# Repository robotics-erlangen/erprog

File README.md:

# ERPROG
This is a JTAG-Programmer developed by the Robot Soccer Team ER-Force from Erlangen, Germany.
The device is using a FTDI chip for communication and a digital isolator for the target.
All necessary files to build and control this device can be found within this repository.

The benefits of this hardware are the easy USB connection with EMC protection and over-current protection. Furthermore the standard JTAG output with a complete isolation up to 4kV. The target isolation is done by two ISO7231M from Texas Instruments. This device also does a voltage translation, which adapts to the target voltage-level. Working is guaranteed from 3.2 to 5.4V.
With this circuit the computer is never effected, if the programming target fails in any way.

Project origin: https://www.robotics-erlangen.de/publications/jtag-programmer

## Hardware

The PCB is designed with EAGLE. The schematic can be found in `erprog_1504-1.sch` and the board in `erprog_1504-1.brd`. The dimension of the PCB is 850mil x 2300mil.

The main ICs are

1.  FT4232HL does the USB to JTAG conversation
2.  ISO7231 is the digital isolator

## Software

The software readme is in https://github.com/robotics-erlangen/erprog/tree/master/software

## Computer connection

**via USB**

The device is connected via a Mini-USB plug to the computer.

## Target connection

**via JTAG**

This hardware uses a JTAG standard connector with a 10 pin connector with the `CoreSight 10` pinout.
Follwoing the pinout is described based on a standard 10 pin 100mil plug with 2 rows.

1.  VTREF
2.  TMS
3.  GND
4.  TCK
5.  GND
6.  TDO
7.  NC
8.  TDI
9.  GND
10. nSRST

## ToDo

For the next release it is planned to allow the controlling of the isolator's enable-pin. Thus, the programmer can be put into high-impedance mode so it does not interfere with the target in normal operation.

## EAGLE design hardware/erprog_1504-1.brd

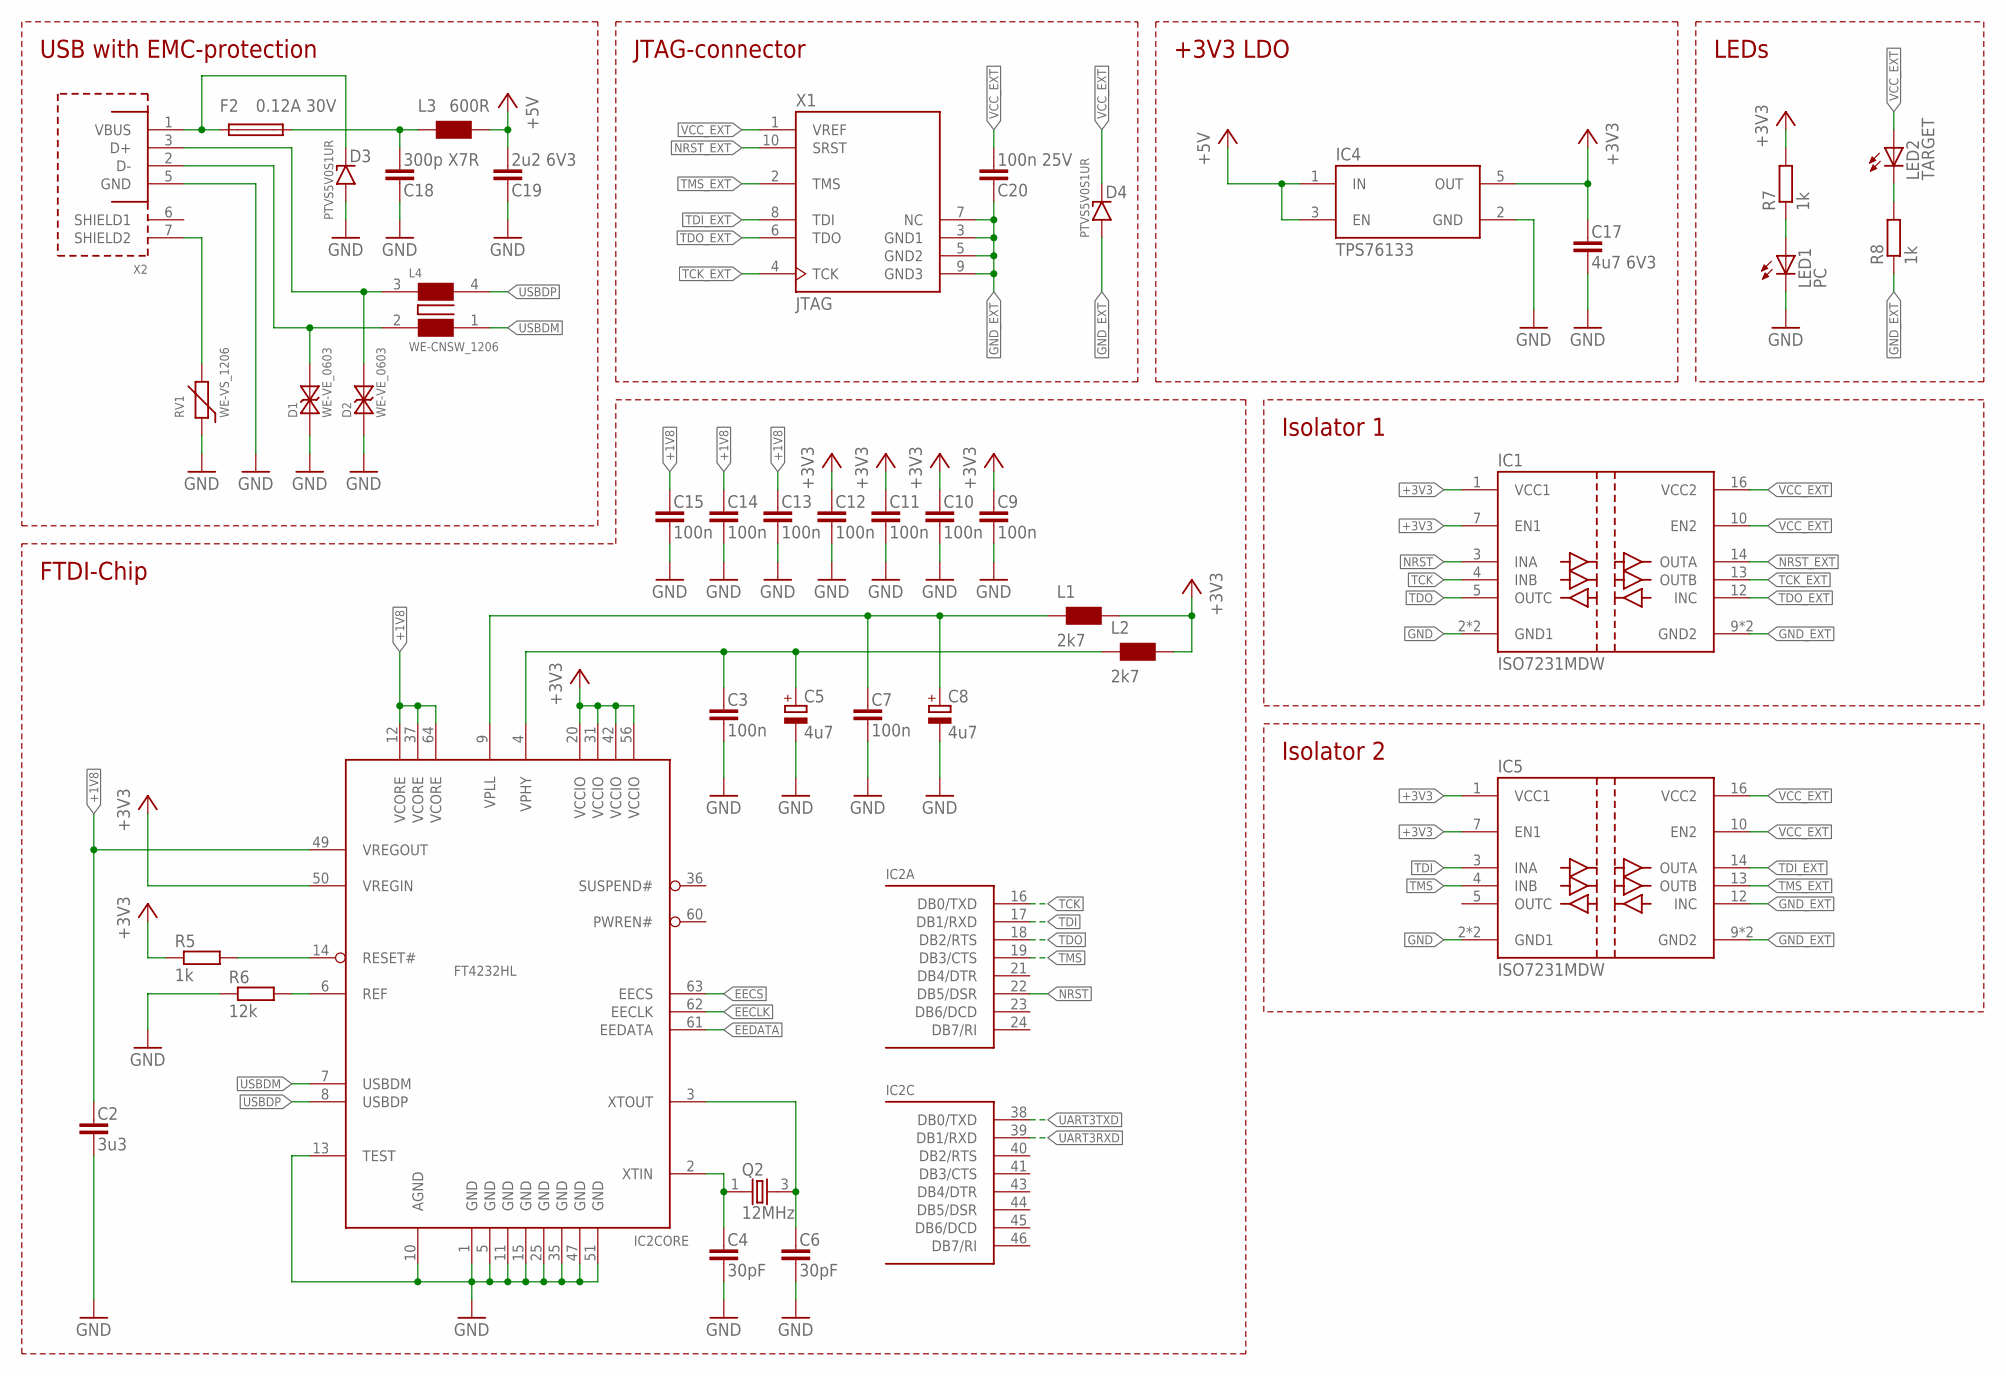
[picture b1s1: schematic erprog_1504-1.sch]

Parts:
C2: 3u3; C0603
C3, C7, C9, C10, C11, C12, C13, C14, C15: 100n; C0603
C4, C6: 30pF; C0603
C5, C8: 4u7; A/3216-18R
C17: 4u7 6V3; C0805
C18: 300p X7R; C0603
C19: 2u2 6V3; C0603
C20: 100n 25V; C0603
D1, D2: WE-VE_0603; WESURGE_0603
D3, D4: PTVS5V0S1UR; SOD123
F2: 0.12A 30V; MF-NSMF-1
IC1, IC5: ISO7231MDW; SO16_SOT162-1
IC2: FT4232HL; LQFP64
IC4: TPS76133; SOT-23-5
L1, L2: 2k7; 0805; FARNELL 1800366
L3: 600R; 0805
L4: WE-CNSW_1206
LED1: PC; SML0805
LED2: TARGET; SML0805
Q2: 12MHz; MQ
R5, R7, R8: 1k; R0603
R6: 12k; R0603
RV1: WE-VS_1206; WESURGE_1206
X1: JTAG; ML10R
X2: USB-SHIELD-MINI-B-BUCHSE-R-ASSMANN; USB-MINI-B-BUCHSE-R

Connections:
+1V8: C2.1, C13.1, C14.1, C15.1, IC2.12 (VCORE), IC2.37 (VCORE), IC2.49 (VREGOUT), IC2.64 (VCORE)
+3V3: C9.1, C10.1, C11.1, C12.1, C17.1, IC1.1 (VCC1), IC1.7 (EN1), IC2.20 (VCCIO), IC2.31 (VCCIO), IC2.42 (VCCIO), IC2.50 (VREGIN), IC2.56 (VCCIO), IC4.5 (OUT), IC5.1 (VCC1), IC5.7 (EN1), L1.2, L2.2, R5.1, R7.2
+5V: C19.2, IC4.1 (IN), IC4.3 (EN), L3.2
EECLK: IC2.62 (EECLK)
EECS: IC2.63 (EECS)
EEDATA: IC2.61 (EEDATA)
GND: C2.2, C3.2, C4.2, C5.-, C6.2, C7.2, C8.-, C9.2, C10.2, C11.2, C12.2, C13.2, C14.2, C15.2, C17.2, C18.1, C19.1, D1.2, D2.2, D3.A (ANODE), IC1.2 (GND1), IC1.8 (GND1), IC2.1 (GND), IC2.5 (GND), IC2.10 (AGND), IC2.11 (GND), IC2.13 (TEST), IC2.15 (GND), IC2.25 (GND), IC2.35 (GND), IC2.47 (GND), IC2.51 (GND), IC4.2 (GND), IC5.2 (GND1), IC5.8 (GND1), LED1.C, R6.1, RV1.1, X2.5 (GND)
GND_EXT: C20.1, D4.A (ANODE), IC1.9 (GND2), IC1.15 (GND2), IC5.9 (GND2), IC5.12 (INC), IC5.15 (GND2), R8.1, X1.3 (GND1), X1.5 (GND2), X1.7 (NC), X1.9 (GND3)
unnamed: D3.C (KATHODE), F2.1, X2.1 (VBUS)
unnamed: LED1.A, R7.1
unnamed: D1.1, L4.2, X2.2 (D-)
unnamed: RV1.2, X2.7 (SHIELD2)
unnamed: LED2.C, R8.2
unnamed: C18.2, F2.2, L3.1
unnamed: D2.1, L4.3 (4), X2.3 (D+)
unnamed: IC2.14 (RESET#), R5.2
unnamed: IC2.6 (REF), R6.2
unnamed: C3.1, C5.+, IC2.4 (VPHY), L2.1
unnamed: C7.1, C8.+, IC2.9 (VPLL), L1.1
unnamed: C6.1, IC2.3 (XTOUT), Q2.3 (2)
unnamed: C4.1, IC2.2 (XTIN), Q2.1
NRST: IC1.3 (INA), IC2.22 (DB5/DSR)
NRST_EXT: IC1.14 (OUTA), X1.10 (SRST)
TCK: IC1.4 (INB), IC2.16 (DB0/TXD)
TCK_EXT: IC1.13 (OUTB), X1.4 (TCK)
TDI: IC2.17 (DB1/RXD), IC5.3 (INA)
TDI_EXT: IC5.14 (OUTA), X1.8 (TDI)
TDO: IC1.5 (OUTC), IC2.18 (DB2/RTS)
TDO_EXT: IC1.12 (INC), X1.6 (TDO)
TMS: IC2.19 (DB3/CTS), IC5.4 (INB)
TMS_EXT: IC5.13 (OUTB), X1.2 (TMS)
UART3RXD: IC2.39 (DB1/RXD)
UART3TXD: IC2.38 (DB0/TXD)
USBDM: IC2.7 (USBDM), L4.1
USBDP: IC2.8 (USBDP), L4.4 (3)
VCC_EXT: C20.2, D4.C (KATHODE), IC1.10 (EN2), IC1.16 (VCC2), IC5.10 (EN2), IC5.16 (VCC2), LED2.A, X1.1 (VREF)

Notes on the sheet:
JTAG-connector
+3V3 LDO
LEDs
USB with EMC-protection
FTDI-Chip
Isolator 1
Isolator 2

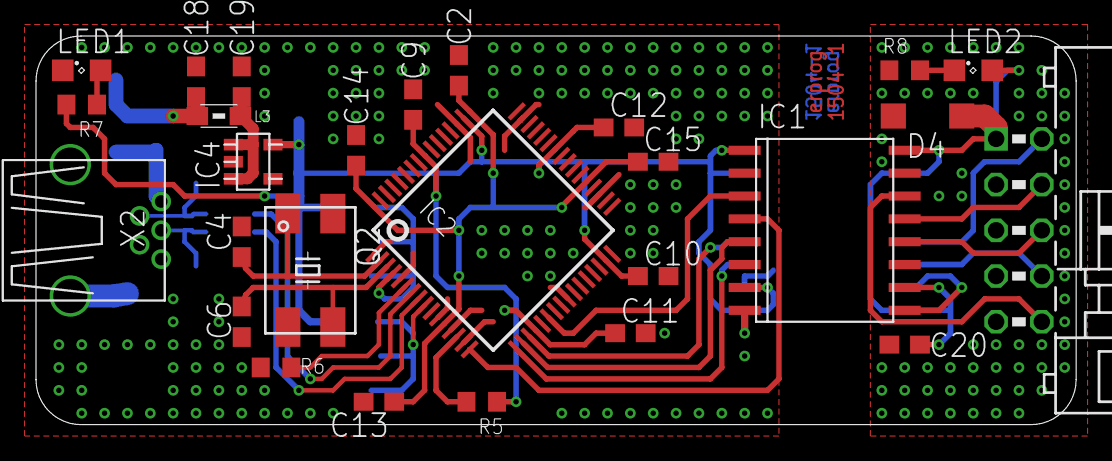
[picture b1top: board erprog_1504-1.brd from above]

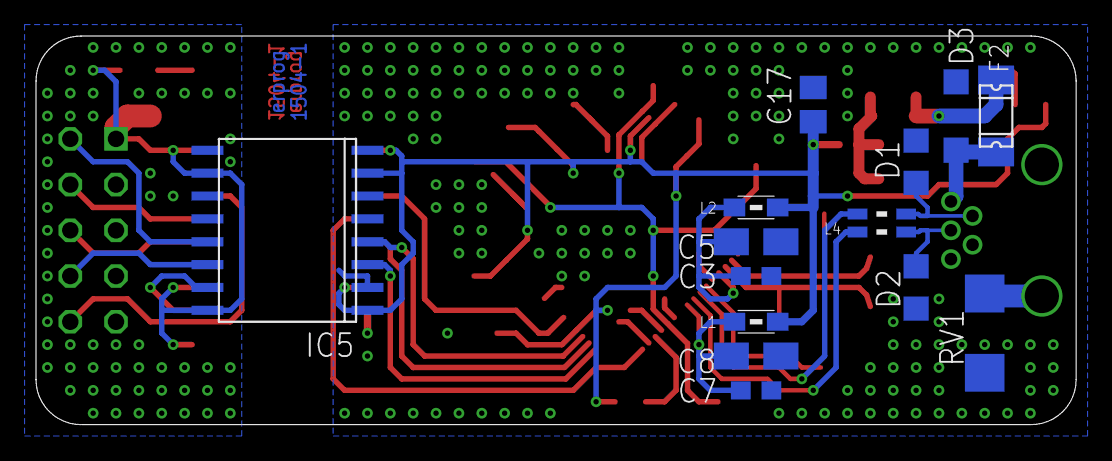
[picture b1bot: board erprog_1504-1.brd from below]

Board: 2 copper layers, 57.8 x 21.6 mm, 41 parts (14 on the bottom side), 31 nets.

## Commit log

2015-04-14 added readme
2015-04-14 added openocd config files
2015-04-14 added software readme
2015-04-14 added board and schematic as EAGLE files
2015-04-14 rearranged names of parts
2015-04-14 added schematic and component diagram as pdfs
2015-04-14 Improve readme for software
2015-06-04 added text to readme
2015-06-04 corrected link notation
2015-06-10 corrected text

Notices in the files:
parts and their libraries:
wuerth_elektronik_v68: Copyright: Würth Elektronik
